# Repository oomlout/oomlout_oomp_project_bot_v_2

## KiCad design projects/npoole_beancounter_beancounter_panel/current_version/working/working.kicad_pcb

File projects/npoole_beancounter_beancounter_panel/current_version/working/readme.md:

# beancounter
 
## summary 
* id: npoole_beancounter_beancounter_panel
* user: npoole
* name: beancounter
* board: beancounter_panel
* repo: https://github.com/NPoole/BeanCounter

* src_file_repo_sch: 
* src_file_repo_sch_link: https://github.com/NPoole/BeanCounter/tree/main/
* full details link: https://github.com/oomlout/oomlout_oomp_project_bot_v_2/tree/main/projects/npoole_beancounter_beancounter_panel/current_version/working  

## pcb  

[board (pdf)](working.pdf)  

## working_bom
| Id | Designator | Footprint | Quantity | Designation | Supplier and ref |  | None | 
| --- | --- | --- | --- | --- | --- | --- | --- | 
| 1 | J5,J7,J15,J19,J10,J16,J11,J9,J23,J21,J22,J3,J8,J17,J20,J6,J4,J18 | 1X01 | 18 |  |  |  | [''] | 
| 2 | D3,D2,D4,D1 | LED-0603 | 4 | IR LED |  |  | [''] | 
| 3 | DIS3,D1S9,D2S2,D1S1,D1S12,D1S3,D2S6,D2S3,D2S1,D3S11,D1S7,D1S4,D3S10,D2S14,D3S5,D3S8,D1S6,D3S1,D1S5,D3S9,D2S8,D3S7,D1S10,D1S8,D2S11,DIS1,D2S7,D3S14,D3S13,D2S10,D3S6,D2S4,D3S2,D1S11,D2S12,D2S9,D2S13,D3S4,D3S12,D2S5,D1S2,D3S3 | LED-0603 | 42 |  |  |  | [''] | 
| 4 | R16,R3,R5,R7,R18,R2,R6,R17,R8,R21,R20,R4,R22,R19 | 0603 | 14 | 33 |  |  | [''] | 
| 5 | R26,R28,R11,R27,R14,R10,R12,R29,R9,R25,R30,R15,R23,R24,R13,R1 | 0603 | 16 | 1k |  |  | [''] | 
| 6 | E$3,E$1,E$2,E$4 | FIDUCIAL-1X2 | 4 |  |  |  | [''] | 
| 7 | Q4,Q2,Q5,Q6,Q3,Q1 | SOT23-3 | 6 | 220mA/50V/3.5Î© |  |  | [''] | 
| 8 | U$31,U$32,U$63,U$64 | HARVATEK_DETECTOR | 4 | B19H1PT |  |  | [''] | 
| 9 | @HOLE0,@HOLE1,@HOLE3,@HOLE2 |  | 4 |  |  |  | [''] | 
| 10 | U1,U2 | 32M1-A_ATM | 2 | ATTINY861V-10MU |  |  | [''] | 
| 11 | S4,S5,S1,S2 | TACTILE_SWITCH_SMD_5.2MM | 4 | MOMENTARY-SWITCH-SPST-SMD-5.2MM-TALL |  |  | [''] | 
| 12 | J12,J24,J14,J2 | 1X02 | 4 |  |  |  | [''] | 
| 13 | C3,C6,C1,C4,C2,C5 | 0603 | 6 | 0.1uF |  |  | [''] | 
| 14 | E$5,E$6 | FIDUCIAL-1.5X3 | 2 |  |  |  | [''] | 
| 15 | S6,S3 | SWITCH_SPST_SMD_A | 2 |  |  |  | [''] | 
| 16 | U$13,U$48 | BY_PRESSING_COUNT#RESET_AGAIN0 | 2 |  |  |  | [''] | 
| 17 | U$53,U$16 | TO_ENTER_COUNTING_MODE_SELECTION0 | 2 |  |  |  | [''] | 
| 18 | U$27,U$59 | #COUNT#0 | 2 |  |  |  | [''] | 
| 19 | U$26,U$58 | #COMPLETE_DOCS_AT_GITHUB#COM#NPOOLE#BEANCOUNTER#0 | 2 |  |  |  | [''] | 
| 20 | U$29,U$61 | #SETUP#0 | 2 |  |  |  | [''] | 
| 21 | U$33,U$6 | #_3V#0 | 2 |  |  |  | [''] | 
| 22 | U$4,U$49 | #PRESS_SETUP_X1#0 | 2 |  |  |  | [''] | 
| 23 | U$50,U$14 | TO_ENTER_PART_PITCH_SETUP0 | 2 |  |  |  | [''] | 
| 24 | U$25,U$57 | ALL_DIGITS_ARE_BLINKING0 | 2 |  |  |  | [''] | 
| 25 | U$36,U$20 | 40 | 2 |  |  |  | [''] | 
| 26 | U$9,U$44 | BY_PRESSING_COUNT#RESET0 | 2 |  |  |  | [''] | 
| 27 | U$24,U$40 | #OFF#EXT#0 | 2 |  |  |  | [''] | 
| 28 | U$35,U$5 | 00 | 2 |  |  |  | [''] | 
| 29 | U$47,U$12 | #RESUME_COUNTING#0 | 2 |  |  |  | [''] | 
| 30 | U$46,U$11 | #_0 | 2 |  |  |  | [''] | 
| 31 | U$39,U$23 | #ON#0 | 2 |  |  |  | [''] | 
| 32 | U$18,U$55 | #RESET_COUNTER#0 | 2 |  |  |  | [''] | 
| 33 | U$60,U$28 | #RESET#0 | 2 |  |  |  | [''] | 
| 34 | U$51,U$8 | THEN_PRESS_COUNT#RESET_TO_INCREMENT0 | 2 |  |  |  | [''] | 
| 35 | U$34,U$7 | #_GND#0 | 2 |  |  |  | [''] | 
| 36 | U$15,U$52 | #PRESS_SETUP_X2#0 | 2 |  |  |  | [''] | 
| 37 | J1,J13 | 2X3_TEST_POINTS | 2 | AVR_SPI_PROG_3X2TESTPOINTS |  |  | [''] | 
| 38 | U$37,U$21 | 120 | 2 |  |  |  | [''] | 
| 39 | U$1,U$41 | OSHWBC#SVG0 | 2 |  |  |  | [''] | 
| 40 | U$56,U$19 | BY_HOLDING_COUNT#RESET_UNTIL0 | 2 |  |  |  | [''] | 
| 41 | U$42,U$2 | EXTERN_PWR0 | 2 |  |  |  | [''] | 
| 42 | U$62,U$30 | LOGO#SVG0 | 2 |  |  |  | [''] | 
| 43 | U$22,U$38 | 160 | 2 |  |  |  | [''] | 
| 44 | BT1,BT2 | BATTCON_20MM_4LEGS_OVERPASTE_INNER | 2 |  |  |  | [''] | 
| 45 | U$17,U$54 | THEN_PRESS_COUNT#RESET_TO_SELECT0 | 2 |  |  |  | [''] | 
| 46 | U$10,U$45 | FIRST_DIGIT_WILL_BLINK_WHILE_PAUSED#_0 | 2 |  |  |  | [''] | 
| 47 | U$3,U$43 | #PAUSE_COUNTING#0 | 2 |  |  |  | [''] |

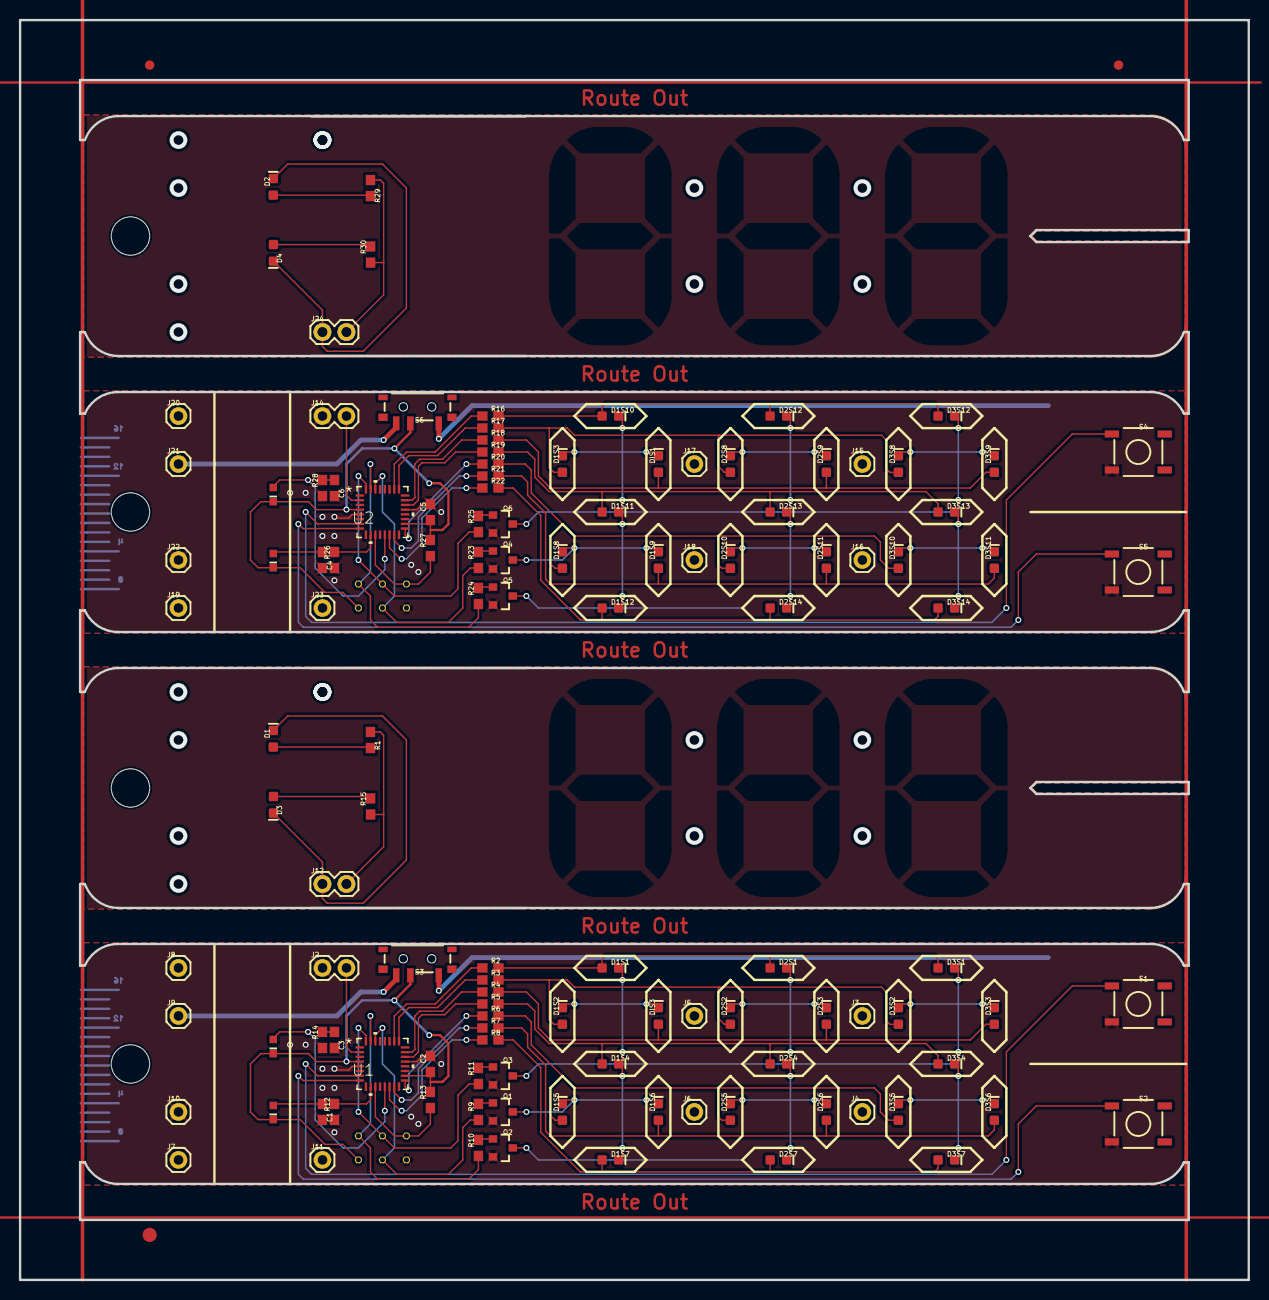
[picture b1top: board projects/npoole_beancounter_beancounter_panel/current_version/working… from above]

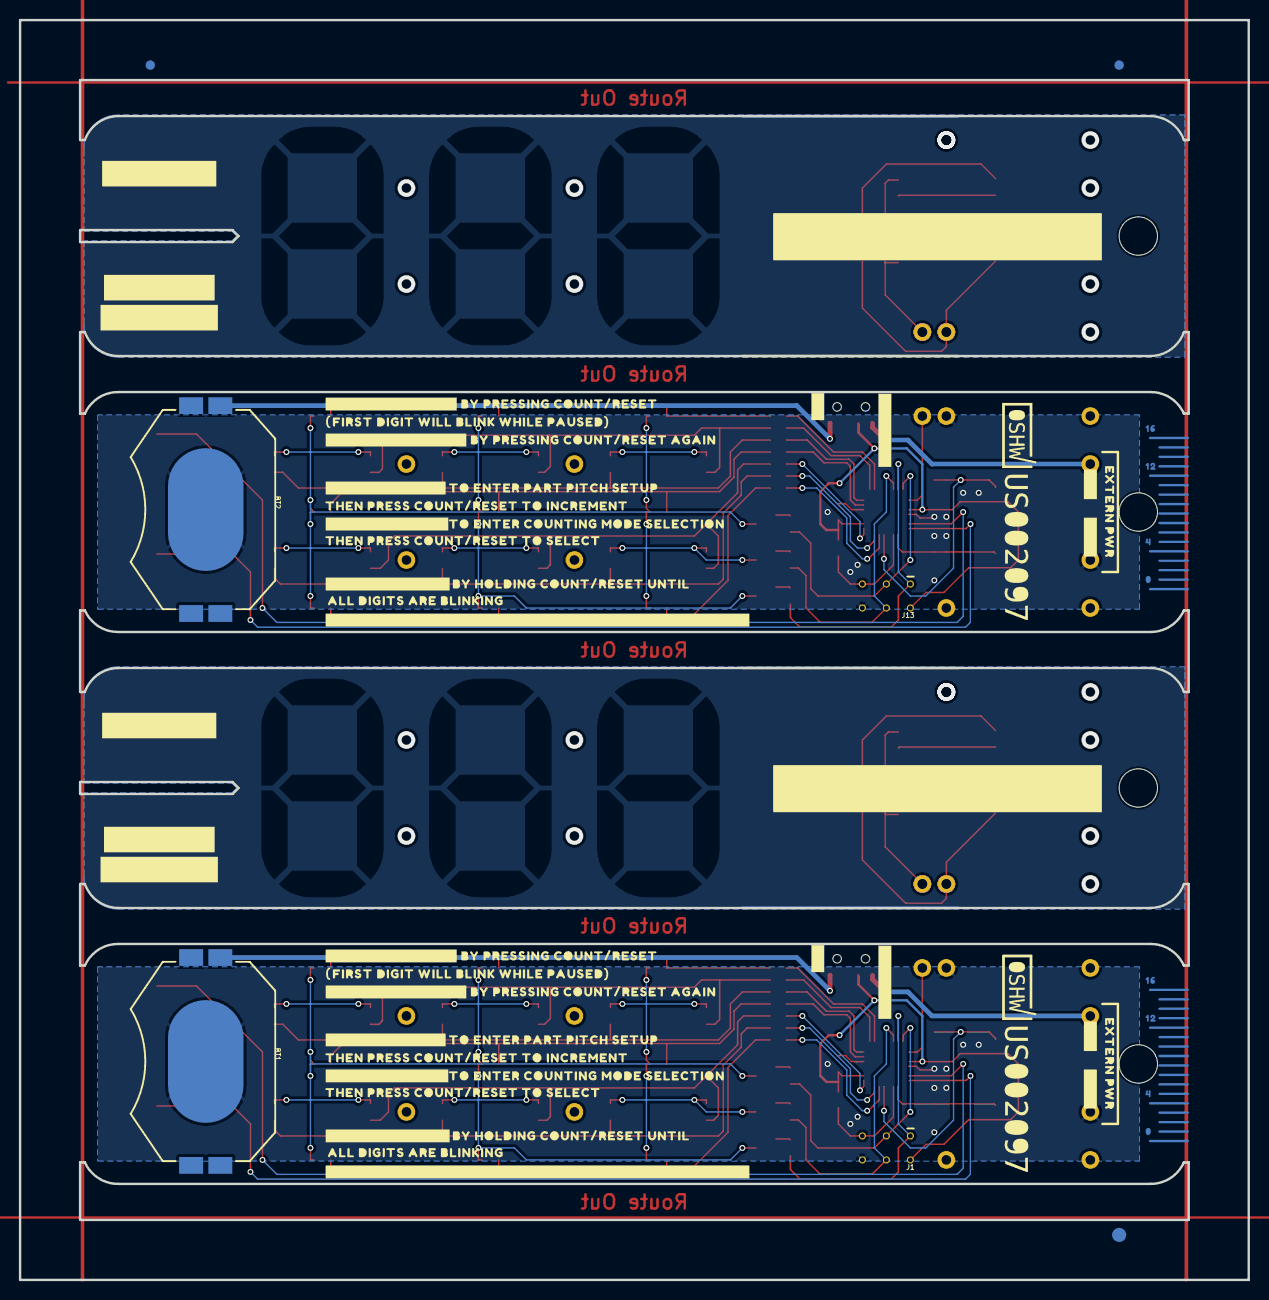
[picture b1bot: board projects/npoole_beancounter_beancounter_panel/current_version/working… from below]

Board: 2 copper layers, 130.0 x 133.3 mm, 196 parts (67 on the bottom side), 74 nets.

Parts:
@HOLE0, @HOLE1, @HOLE2, @HOLE3: (no value)
BT1, BT2: BATTCON_20MM_4LEGS_OVERPASTE_INNER
C1, C2, C3, C4, C5, C6: 0.1uF; 0603
D1, D2, D3, D4: IR LED; LED-0603
D1S1, D1S2, D1S3, D1S4, D1S5, D1S6, D1S7, D1S8, D1S9, D1S10, D1S11, D1S12, D2S1, D2S2, D2S3, D2S4, D2S5, D2S6, D2S7, D2S8, D2S9, D2S10, D2S11, D2S12, D2S13, D2S14, D3S1, D3S2, D3S3, D3S4, D3S5, D3S6, D3S7, D3S8, D3S9, D3S10, D3S11, D3S12, D3S13, D3S14: LED-0603
DIS1, DIS3: LED-0603
E$1, E$2, E$3, E$4: FIDUCIAL-1X2
E$5, E$6: FIDUCIAL-1.5X3
J1, J13: AVR_SPI_PROG_3X2TESTPOINTS; 2X3_TEST_POINTS
J2, J12, J14, J24: 1X02
J3, J4, J5, J6, J7, J8, J9, J10, J11, J15, J16, J17, J18, J19, J20, J21, J22, J23: 1X01
Q1, Q2, Q3, Q4, Q5, Q6: 220mA/50V/3.5Ω; SOT23-3
R1, R9, R10, R11, R12, R13, R14, R15, R23, R24, R25, R26, R27, R28, R29, R30: 1k; 0603
R2, R3, R4, R5, R6, R7, R8, R16, R17, R18, R19, R20, R21, R22: 33; 0603
S1, S2, S4, S5: MOMENTARY-SWITCH-SPST-SMD-5.2MM-TALL; TACTILE_SWITCH_SMD_5.2MM
S3, S6: SWITCH_SPST_SMD_A
U1, U2: ATTINY861V-10MU; 32M1-A_ATM
U$1, U$41: OSHWBC#SVG0
U$2, U$42: EXTERN_PWR0
U$3, U$43: #PAUSE_COUNTING#0
U$4, U$49: #PRESS_SETUP_X1#0
U$5, U$35: 00
U$6, U$33: #_3V#0
U$7, U$34: #_GND#0
U$8, U$51: THEN_PRESS_COUNT#RESET_TO_INCREMENT0
U$9, U$44: BY_PRESSING_COUNT#RESET0
U$10, U$45: FIRST_DIGIT_WILL_BLINK_WHILE_PAUSED#_0
U$11, U$46: #_0
U$12, U$47: #RESUME_COUNTING#0
U$13, U$48: BY_PRESSING_COUNT#RESET_AGAIN0
U$14, U$50: TO_ENTER_PART_PITCH_SETUP0
U$15, U$52: #PRESS_SETUP_X2#0
U$16, U$53: TO_ENTER_COUNTING_MODE_SELECTION0
U$17, U$54: THEN_PRESS_COUNT#RESET_TO_SELECT0
U$18, U$55: #RESET_COUNTER#0
U$19, U$56: BY_HOLDING_COUNT#RESET_UNTIL0
U$20, U$36: 40
U$21, U$37: 120
U$22, U$38: 160
U$23, U$39: #ON#0
U$24, U$40: #OFF#EXT#0
U$25, U$57: ALL_DIGITS_ARE_BLINKING0
U$26, U$58: #COMPLETE_DOCS_AT_GITHUB#COM#NPOOLE#BEANCOUNTER#0
U$27, U$59: #COUNT#0
U$28, U$60: #RESET#0
U$29, U$61: #SETUP#0
U$30, U$62: LOGO#SVG0
U$31, U$32, U$63, U$64: B19H1PT; HARVATEK_DETECTOR

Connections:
0: R2.1, U1.26
1: R3.1, U1.25
2: R4.1, U1.23
3: R5.1, U1.22
4: R6.1, U1.17
5: R7.1, U1.15
6: R8.1, U1.14
8/COPI: J1.4, R9.1, U1.30
9/CIPO: J1.1, R10.1, U1.31
10/SCK: J1.3, R11.1, U1.32
11: J2.2, U1.2
12: S1.1, U1.7
13: S2.1, U1.8
GND: BT1.2, C1.2, C2.2, C3.2, J1.6, J2.1, J10.1, Q1.2, Q2.2, Q3.2, R12.1, R14.1, S1.3, S2.3, U1.5, U1.21
IR_DETECTOR_A: C1.1, R12.2, U1.10, U$31.P$2
IR_DETECTOR_B: C3.1, R14.2, U1.13, U$32.P$2
unnamed: BT1.1, S3.3
unnamed: D1S1.C, D1S2.C, D1S4.C, D1S5.C, D1S6.C, D1S7.C, DIS3.C, Q1.3
unnamed: Q2.1, R10.2
unnamed: Q1.1, R9.2
unnamed: D2S1.C, D2S2.C, D2S3.C, D2S4.C, D2S5.C, D2S6.C, D2S7.C, Q2.3
unnamed: Q3.1, R11.2
unnamed: D3S1.C, D3S2.C, D3S3.C, D3S4.C, D3S5.C, D3S6.C, D3S7.C, Q3.3
unnamed: C6.1, R28.2, U2.13, U$64.P$2
unnamed: J24.2, R29.1, R30.1
unnamed: D2.C, D4.C, J24.1
unnamed: J12.2, R1.1, R15.1
unnamed: D1.C, D3.C, J12.1
unnamed: D3.A, R15.2
unnamed: D1.A, R1.2
unnamed: BT2.2, C4.2, C5.2, C6.2, J13.6, J14.1, J22.1, Q4.2, Q5.2, Q6.2, R26.1, R28.1, S4.3, S5.3, U2.5, U2.21
unnamed: C5.1, J13.2, R27.2, S6.2, U2.4, U2.18, U$63.P$1, U$64.P$1
unnamed: Q4.1, R23.2
unnamed: D1S3.C, D1S8.C, D1S9.C, D1S10.C, D1S11.C, D1S12.C, DIS1.C, Q4.3
unnamed: D2S8.C, D2S9.C, D2S10.C, D2S11.C, D2S12.C, D2S13.C, D2S14.C, Q5.3
unnamed: D3S8.C, D3S9.C, D3S10.C, D3S11.C, D3S12.C, D3S13.C, D3S14.C, Q6.3
unnamed: Q5.1, R24.2
unnamed: Q6.1, R25.2
unnamed: D1S10.A, D2S12.A, D3S12.A, R16.2
unnamed: D1S11.A, D2S13.A, D3S13.A, R19.2
unnamed: D1S3.A, D2S8.A, D3S8.A, R17.2
unnamed: D2S9.A, D3S9.A, DIS1.A, R18.2
unnamed: D1S9.A, D2S11.A, D3S11.A, R21.2
unnamed: D1S8.A, D2S10.A, D3S10.A, R20.2
unnamed: D1S12.A, D2S14.A, D3S14.A, R22.2
unnamed: C4.1, R26.2, U2.10, U$63.P$2
unnamed: J13.5, R27.1, U2.11
unnamed: R16.1, U2.26
unnamed: R17.1, U2.25
unnamed: R18.1, U2.23
unnamed: R19.1, U2.22
unnamed: R20.1, U2.17
unnamed: R21.1, U2.15
unnamed: R22.1, U2.14
unnamed: J13.4, R23.1, U2.30
unnamed: J13.1, R24.1, U2.31
unnamed: J13.3, R25.1, U2.32
unnamed: J14.2, U2.2
unnamed: S4.1, U2.7
unnamed: S5.1, U2.8
unnamed: J21.1, S6.1
unnamed: BT2.1, S6.3
SEG1: D1S1.A, D2S1.A, D3S1.A, R2.2
SEG2: D1S2.A, D2S2.A, D3S2.A, R3.2
SEG3: D2S3.A, D3S3.A, DIS3.A, R4.2
SEG4: D1S4.A, D2S4.A, D3S4.A, R5.2
SEG5: D1S5.A, D2S5.A, D3S5.A, R6.2
SEG6: D1S6.A, D2S6.A, D3S6.A, R7.2
SEG7: D1S7.A, D2S7.A, D3S7.A, R8.2
SEG9: D4.A, R30.2
SEG10: D2.A, R29.2
V_BATT: C2.1, J1.2, R13.2, S3.2, U1.4, U1.18, U$31.P$1, U$32.P$1
V_EXT: J9.1, S3.1
~RESET: J1.5, R13.1, U1.11

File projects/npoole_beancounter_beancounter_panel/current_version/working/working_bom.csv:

"Id";"Designator";"Footprint";"Quantity";"Designation";"Supplier and ref";
1;"J5,J7,J15,J19,J10,J16,J11,J9,J23,J21,J22,J3,J8,J17,J20,J6,J4,J18";"1X01";18;"";;;
2;"D3,D2,D4,D1";"LED-0603";4;"IR LED";;;
3;"DIS3,D1S9,D2S2,D1S1,D1S12,D1S3,D2S6,D2S3,D2S1,D3S11,D1S7,D1S4,D3S10,D2S14,D3S5,D3S8,D1S6,D3S1,D1S5,D3S9,D2S8,D3S7,D1S10,D1S8,D2S11,DIS1,D2S7,D3S14,D3S13,D2S10,D3S6,D2S4,D3S2,D1S11,D2S12,D2S9,D2S13,D3S4,D3S12,D2S5,D1S2,D3S3";"LED-0603";42;"";;;
4;"R16,R3,R5,R7,R18,R2,R6,R17,R8,R21,R20,R4,R22,R19";"0603";14;"33";;;
5;"R26,R28,R11,R27,R14,R10,R12,R29,R9,R25,R30,R15,R23,R24,R13,R1";"0603";16;"1k";;;
6;"E$3,E$1,E$2,E$4";"FIDUCIAL-1X2";4;"";;;
7;"Q4,Q2,Q5,Q6,Q3,Q1";"SOT23-3";6;"220mA/50V/3.5Ω";;;
8;"U$31,U$32,U$63,U$64";"HARVATEK_DETECTOR";4;"B19H1PT";;;
9;"@HOLE0,@HOLE1,@HOLE3,@HOLE2";"";4;"";;;
10;"U1,U2";"32M1-A_ATM";2;"ATTINY861V-10MU";;;
11;"S4,S5,S1,S2";"TACTILE_SWITCH_SMD_5.2MM";4;"MOMENTARY-SWITCH-SPST-SMD-5.2MM-TALL";;;
12;"J12,J24,J14,J2";"1X02";4;"";;;
13;"C3,C6,C1,C4,C2,C5";"0603";6;"0.1uF";;;
14;"E$5,E$6";"FIDUCIAL-1.5X3";2;"";;;
15;"S6,S3";"SWITCH_SPST_SMD_A";2;"";;;
16;"U$13,U$48";"BY_PRESSING_COUNT#RESET_AGAIN0";2;"";;;
17;"U$53,U$16";"TO_ENTER_COUNTING_MODE_SELECTION0";2;"";;;
18;"U$27,U$59";"#COUNT#0";2;"";;;
19;"U$26,U$58";"#COMPLETE_DOCS_AT_GITHUB#COM#NPOOLE#BEANCOUNTER#0";2;"";;;
20;"U$29,U$61";"#SETUP#0";2;"";;;
21;"U$33,U$6";"#_3V#0";2;"";;;
22;"U$4,U$49";"#PRESS_SETUP_X1#0";2;"";;;
23;"U$50,U$14";"TO_ENTER_PART_PITCH_SETUP0";2;"";;;
24;"U$25,U$57";"ALL_DIGITS_ARE_BLINKING0";2;"";;;
25;"U$36,U$20";"40";2;"";;;
26;"U$9,U$44";"BY_PRESSING_COUNT#RESET0";2;"";;;
27;"U$24,U$40";"#OFF#EXT#0";2;"";;;
28;"U$35,U$5";"00";2;"";;;
29;"U$47,U$12";"#RESUME_COUNTING#0";2;"";;;
30;"U$46,U$11";"#_0";2;"";;;
31;"U$39,U$23";"#ON#0";2;"";;;
32;"U$18,U$55";"#RESET_COUNTER#0";2;"";;;
33;"U$60,U$28";"#RESET#0";2;"";;;
34;"U$51,U$8";"THEN_PRESS_COUNT#RESET_TO_INCREMENT0";2;"";;;
35;"U$34,U$7";"#_GND#0";2;"";;;
36;"U$15,U$52";"#PRESS_SETUP_X2#0";2;"";;;
37;"J1,J13";"2X3_TEST_POINTS";2;"AVR_SPI_PROG_3X2TESTPOINTS";;;
38;"U$37,U$21";"120";2;"";;;
39;"U$1,U$41";"OSHWBC#SVG0";2;"";;;
40;"U$56,U$19";"BY_HOLDING_COUNT#RESET_UNTIL0";2;"";;;
41;"U$42,U$2";"EXTERN_PWR0";2;"";;;
42;"U$62,U$30";"LOGO#SVG0";2;"";;;
43;"U$22,U$38";"160";2;"";;;
44;"BT1,BT2";"BATTCON_20MM_4LEGS_OVERPASTE_INNER";2;"";;;
45;"U$17,U$54";"THEN_PRESS_COUNT#RESET_TO_SELECT0";2;"";;;
46;"U$10,U$45";"FIRST_DIGIT_WILL_BLINK_WHILE_PAUSED#_0";2;"";;;
47;"U$3,U$43";"#PAUSE_COUNTING#0";2;"";;;

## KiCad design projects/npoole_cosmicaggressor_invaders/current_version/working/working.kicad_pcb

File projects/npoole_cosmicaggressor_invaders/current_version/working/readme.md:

# cosmicaggressor
 
## summary 
* id: npoole_cosmicaggressor_invaders
* user: npoole
* name: cosmicaggressor
* board: invaders
* repo: https://github.com/NPoole/CosmicAggressor

* src_file_repo_sch: 
* src_file_repo_sch_link: https://github.com/NPoole/CosmicAggressor/tree/master/
* full details link: https://github.com/oomlout/oomlout_oomp_project_bot_v_2/tree/main/projects/npoole_cosmicaggressor_invaders/current_version/working  

## schematic  
  
[schematic (pdf)](working_schematic.pdf) 

## pcb  

[board (pdf)](working.pdf)  

## working_bom
| Id | Designator | Footprint | Quantity | Designation | Supplier and ref |  | None | 
| --- | --- | --- | --- | --- | --- | --- | --- | 
| 1 | D72,D84,D8,D46,D67,D22,D29,D92,D126,D20,D68,D66,D52,D87,D108,D99,D95,D2,D57,D100,D127,D120,D117,D38,D102,D137,D31,D61,D17,D3,D65,D121,D37,D30,D85,D103,D98,D33,D140,D79,D41,D1,D81,D77,D40,D11,D75,D19,D47,D74,D62,D49,D93,D128,D109,D141,D143,D42,D56,D54,D71,D115,D78,D111,D124,D114,D110,D50,D144,D24,D26,D5,D107,D35,D4,D76,D43,D28,D7,D104,D45,D101,D63,D90,D122,D60,D51,D15,D55,D16,D116,D48,D39,D80,D34,D23,D32,D123,D112,D12,D96,D105,D10,D142,D58,D113,D9,D25,D125,D106,D94,D53,D86,D139,D36,D118,D18,D44,D13,D64,D73,D59,D138,D69,D21,D6,D27,D82,D70,D119,D91,D89,D97,D88,D83,D14 | APA102-2020 | 136 | APA102-2020 |  |  | [''] | 
| 2 | C9,C10 | 0603 | 2 | 4.7uF |  |  | [''] | 
| 3 | U2 | SOT23-5 | 1 | MCP73831 |  |  | [''] | 
| 4 | R3,R2 | 0603@1 | 2 | 22 |  |  | [''] | 
| 5 | Y1 | CRYSTAL-SMD-5X3.2-4PAD | 1 | 16MHz |  |  | [''] | 
| 6 | R1 | 0603@1 | 1 | 10k |  |  | [''] | 
| 7 | BT1 | BATTERY_18650-HOLDER | 1 |  |  |  | [''] | 
| 8 | J9,J6,J5,J8,J4,J7,J2,J3 | 1X01NS_KIT | 8 |  |  |  | [''] | 
| 9 | D131,D130 | SMA-DIODE | 2 | 3A/40V/500mV |  |  | [''] | 
| 10 | C2,C3 | 0603 | 2 | 1.0uF |  |  | [''] | 
| 11 | C8,C6,C7 | 0805 | 3 | 22uF |  |  | [''] | 
| 12 | C4,C5 | 0603 | 2 | 18pF |  |  | [''] | 
| 13 | R6,R4 | 0603 | 2 | 750K |  |  | [''] | 
| 14 | RPROG0 | 0603 | 1 | 2.0k |  |  | [''] | 
| 15 | R5 | 0603 | 1 | 100k |  |  | [''] | 
| 16 | C1 | 0603 | 1 | 0.1uF |  |  | [''] | 
| 17 | U3 | MSOP8 | 1 | PAM2401 |  |  | [''] | 
| 18 | L1 | INDUCTOR_4X4MM | 1 | 2.2UH3A |  |  | [''] | 
| 19 | J1 | USB-MICROB-PTH-MILL | 1 |  |  |  | [''] | 
| 20 | U1 | QFN-44-NOPAD_1_1-LESS_PASTE | 1 | 32U4 |  |  | [''] | 
| 21 | S2 | SWITCH_DPDT_SMD_AYZ0202 | 1 |  |  |  | [''] | 
| 22 | U$1 | COSMIC_AGGRESSOR0 | 1 |  |  |  | [''] | 
| 23 | J10 | 2X3 | 1 | AVR_SPI_PROG_3X2PTH |  |  | [''] | 
| 24 | U$2 | #NORTHALLENPOOLE1 | 1 |  |  |  | [''] | 
| 25 | U$4 | OSHW-LOGO-S | 1 |  |  |  | [''] | 
| 26 | U$3 | HTTPS###GITHUB#COM#NPOOLE#COSMICAGGRESSOR2 | 1 |  |  |  | [''] | 

## bom_schematic
| Ref | Qnty | Value | Cmp name | Footprint | Description | Vendor | DNP | 
| --- | --- | --- | --- | --- | --- | --- | --- | 
| BT1 | 1 | BATTERY-18650 | BATTERY-18650 | working:BATTERY_18650-HOLDER |  |  |  | 
| C1 | 1 | 0.1UF-0603-25V-(+80/-20%) | 0.1UF-0603-25V-(+80/-20%) | working:0603 |  |  |  | 
| C2, C3 | 2 | 1.0UF-0603-16V-10% | 1.0UF-0603-16V-10% | working:0603 |  |  |  | 
| C4, C5 | 2 | 18PF-0603-50V-5% | 18PF-0603-50V-5% | working:0603 |  |  |  | 
| C6, C7, C8 | 3 | 22UF-0805-6.3V-20% | 22UF-0805-6.3V-20% | working:0805 |  |  |  | 
| C9, C10 | 2 | 4.7UF0603 | 4.7UF0603 | working:0603 |  |  |  | 
| D1, D2, D3, D4, D5, D6, D7, D8, D9, D10, D11, D12, D13, D14, D15, D16, D17, D18, D19, D20, D21, D22, D23, D24, D25, D26, D27, D28, D29, D30, D31, D32, D33, D34, D35, D36, D37, D38, D39, D40, D41, D42, D43, D44, D45, D46, D47, D48, D49, D50, D51, D52, D53, D54, D55, D56, D57, D58, D59, D60, D61, D62, D63, D64, D65, D66, D67, D68, D69, D70, D71, D72, D73, D74, D75, D76, D77, D78, D79, D80, D81, D82, D83, D84, D85, D86, D87, D88, D89, D90, D91, D92, D93, D94, D95, D96, D97, D98, D99, D100, D101, D102, D103, D104, D105, D106, D107, D108, D109, D110, D111, D112, D113, D114, D115, D116, D117, D118, D119, D120, D121, D122, D123, D124, D125, D126, D127, D128, D137, D138, D139, D140, D141, D142, D143, D144 | 136 | APA102-2020 | APA102-2020 | working:APA102-2020 |  |  |  | 
| D130, D131 | 2 | DIODE-SCHOTTKY-B340A | DIODE-SCHOTTKY-B340A | working:SMA-DIODE |  |  |  | 
| J1 | 1 | USB_MICRO-B_HALF_PTH_MILL | USB_MICRO-B_HALF_PTH_MILL | working:USB-MICROB-PTH-MILL |  |  |  | 
| J2, J3, J4, J5, J6, J7, J8, J9 | 8 | CONN_01PTH_NO_SILK_KIT | CONN_01PTH_NO_SILK_KIT | working:1X01NS_KIT |  |  |  | 
| J10 | 1 | AVR_SPI_PROG_3X2PTH | AVR_SPI_PROG_3X2PTH | working:2X3 |  |  |  | 
| L1 | 1 | INDUCTOR-IFSC1515AHER2R2M01 | INDUCTOR-IFSC1515AHER2R2M01 | working:INDUCTOR_4X4MM |  |  |  | 
| R1 | 1 | 10KOHM-0603-1/10W-1% | 10KOHM-0603-1/10W-1% | working:0603@1 |  |  |  | 
| R2, R3 | 2 | 22OHM-0603-1/10W-1% | 22OHM-0603-1/10W-1% | working:0603@1 |  |  |  | 
| R4, R6 | 2 | 750KOHM-0603-1/10W-1% | 750KOHM-0603-1/10W-1% | working:0603 |  |  |  | 
| R5 | 1 | 100KOHM-0603-1/10W-1% | 100KOHM-0603-1/10W-1% | working:0603 |  |  |  | 
| RPROG0 | 1 | 2.0KOHM-0603-1/10W-5% | 2.0KOHM-0603-1/10W-5% | working:0603 |  |  |  | 
| S2 | 1 | SWITCH-DPDT-SMD-AYZ0202 | SWITCH-DPDT-SMD-AYZ0202 | working:SWITCH_DPDT_SMD_AYZ0202 |  |  |  | 
| U1 | 1 | ATMEGA32U41:1-LESS_PASTE | ATMEGA32U41{colon}1-LESS_PASTE | working:QFN-44-NOPAD_1_1-LESS_PASTE |  |  |  | 
| U2 | 1 | MCP73831 | MCP73831 | working:SOT23-5 |  |  |  | 
| U3 | 1 | PAM2401 | PAM2401 | working:MSOP8 |  |  |  | 
| Y1 | 1 | 16MHz | CRYSTAL-16MHZSMD-5X3.2 | working:CRYSTAL-SMD-5X3.2-4PAD |  |  |  |

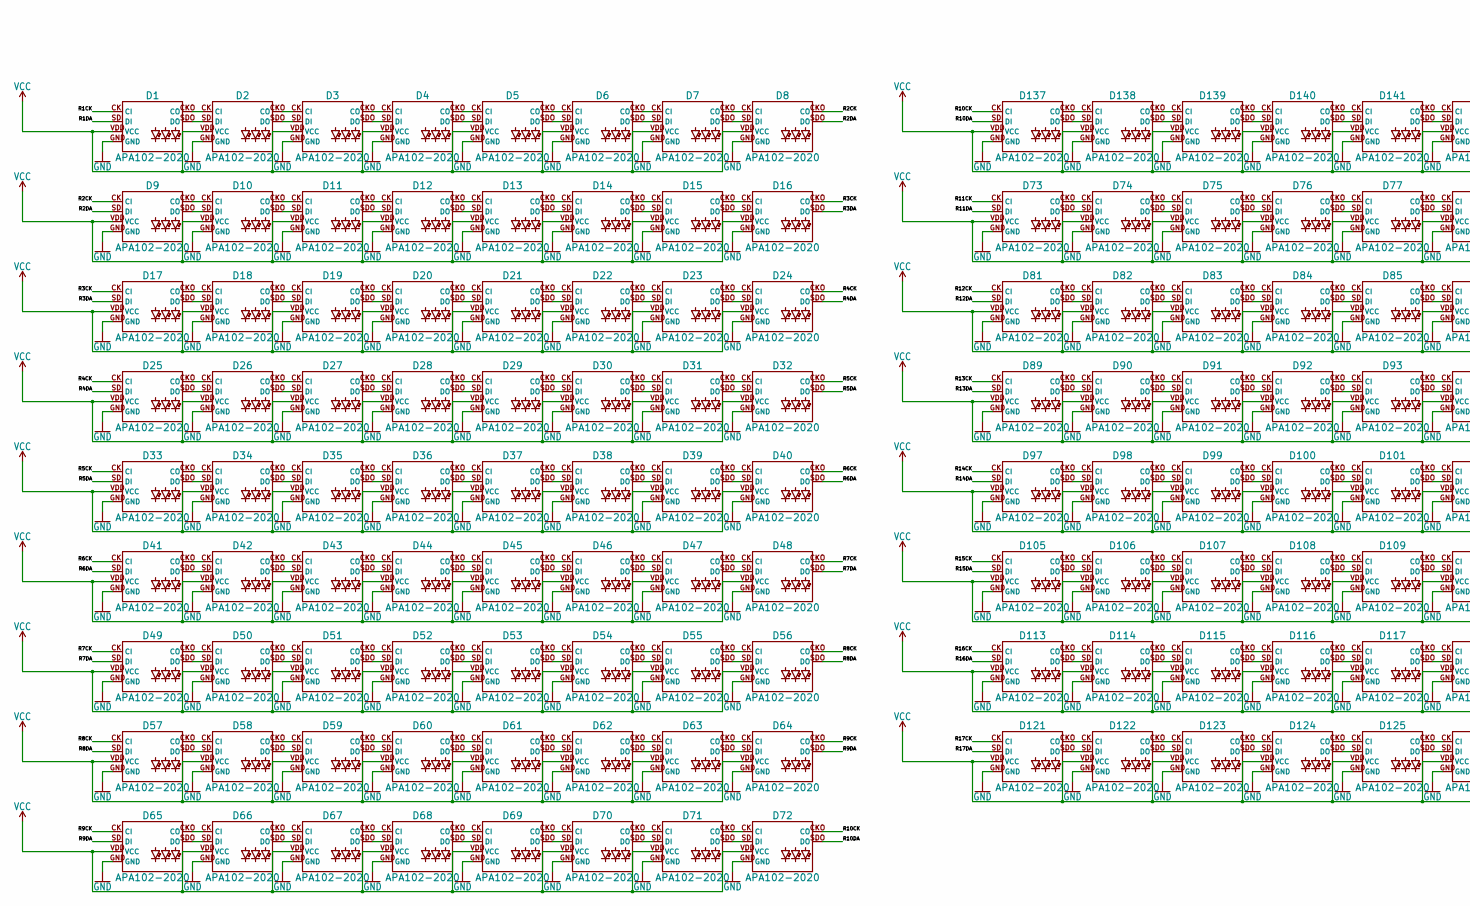
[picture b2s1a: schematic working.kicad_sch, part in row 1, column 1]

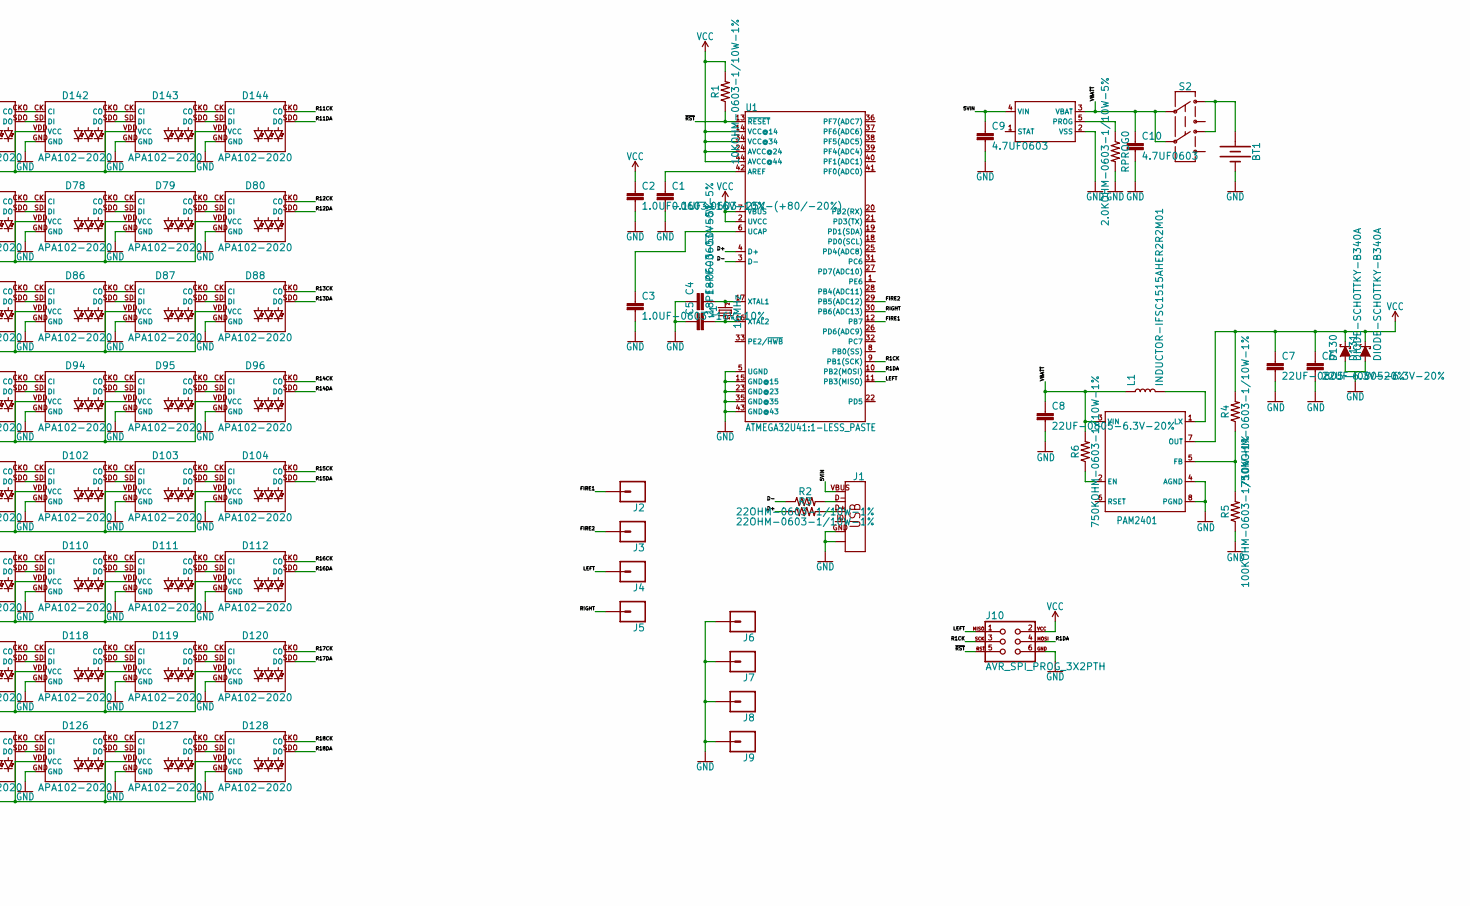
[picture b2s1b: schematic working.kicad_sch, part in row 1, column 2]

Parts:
BT1: BATTERY-18650; BATTERY_18650-HOLDER
C1: 0.1UF-0603-25V-(+80/-20%); 0603
C2, C3: 1.0UF-0603-16V-10%; 0603
C4, C5: 18PF-0603-50V-5%; 0603
C6, C7, C8: 22UF-0805-6.3V-20%; 0805
C9, C10: 4.7UF0603; 0603
D1, D2, D3, D4, D5, D6, D7, D8, D9, D10, D11, D12, D13, D14, D15, D16, D17, D18, D19, D20, D21, D22, D23, D24, D25, D26, D27, D28, D29, D30, D31, D32, D33, D34, D35, D36, D37, D38, D39, D40, D41, D42, D43, D44, D45, D46, D47, D48, D49, D50, D51, D52, D53, D54, D55, D56, D57, D58, D59, D60, D61, D62, D63, D64, D65, D66, D67, D68, D69, D70, D71, D72, D73, D74, D75, D76, D77, D78, D79, D80, D81, D82, D83, D84, D85, D86, D87, D88, D89, D90, D91, D92, D93, D94, D95, D96, D97, D98, D99, D100, D101, D102, D103, D104, D105, D106, D107, D108, D109, D110, D111, D112, D113, D114, D115, D116, D117, D118, D119, D120, D121, D122, D123, D124, D125, D126, D127, D128, D137, D138, D139, D140, D141, D142, D143, D144: APA102-2020
D130, D131: DIODE-SCHOTTKY-B340A; SMA-DIODE
J1: USB_MICRO-B_HALF_PTH_MILL; USB-MICROB-PTH-MILL
J2, J3, J4, J5, J6, J7, J8, J9: CONN_01PTH_NO_SILK_KIT; 1X01NS_KIT
J10: AVR_SPI_PROG_3X2PTH; 2X3
L1: INDUCTOR-IFSC1515AHER2R2M01; INDUCTOR_4X4MM
R1: 10KOHM-0603-1/10W-1%; 0603@1
R2, R3: 22OHM-0603-1/10W-1%; 0603@1
R4, R6: 750KOHM-0603-1/10W-1%; 0603
R5: 100KOHM-0603-1/10W-1%; 0603
RPROG0: 2.0KOHM-0603-1/10W-5%; 0603
S2: SWITCH-DPDT-SMD-AYZ0202; SWITCH_DPDT_SMD_AYZ0202
U1: ATMEGA32U41:1-LESS_PASTE; QFN-44-NOPAD_1_1-LESS_PASTE
U2: MCP73831; SOT23-5
U3: PAM2401; MSOP8
Y1: 16MHz; CRYSTAL-SMD-5X3.2-4PAD

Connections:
5VIN: C9.1, J1.VBUS, U2.4 (VIN)
D+: R3.1, U1.4 (D+)
D-: R2.1, U1.3 (D-)
EN: R6.1, U3.2 (EN)
FIRE1: J2.1, U1.12 (PB7)
FIRE2: J3.1, U1.29 (PB5(ADC12))
GND: BT1.GND@1 (-), C1.2, C2.2, C3.2, C4.1, C5.1, C6.2, C7.2, C8.2, C9.2, C10.2, D1.GND, D2.GND, D3.GND, D4.GND, D5.GND, D6.GND, D7.GND, D8.GND, D9.GND, D10.GND, D11.GND, D12.GND, D13.GND, D14.GND, D15.GND, D16.GND, D17.GND, D18.GND, D19.GND, D20.GND, D21.GND, D22.GND, D23.GND, D24.GND, D25.GND, D26.GND, D27.GND, D28.GND, D29.GND, D30.GND, D31.GND, D32.GND, D33.GND, D34.GND, D35.GND, D36.GND, D37.GND, D38.GND, D39.GND, D40.GND, D41.GND, D42.GND, D43.GND, D44.GND, D45.GND, D46.GND, D47.GND, D48.GND, D49.GND, D50.GND, D51.GND, D52.GND, D53.GND, D54.GND, D55.GND, D56.GND, D57.GND, D58.GND, D59.GND, D60.GND, D61.GND, D62.GND, D63.GND, D64.GND, D65.GND, D66.GND, D67.GND, D68.GND, D69.GND, D70.GND, D71.GND, D72.GND, D73.GND, D74.GND, D75.GND, D76.GND, D77.GND, D78.GND, D79.GND, D80.GND, D81.GND, D82.GND, D83.GND, D84.GND, D85.GND, D86.GND, D87.GND, D88.GND, D89.GND, D90.GND, D91.GND, D92.GND, D93.GND, D94.GND, D95.GND, D96.GND, D97.GND, D98.GND, D99.GND, D100.GND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
LEFT: J4.1, J10.1, U1.11 (PB3(MISO))
unnamed: D73.CKO (CO), D74.CKI (CI)
unnamed: D73.SDO (DO), D74.SDI (DI)
unnamed: D1.CKO (CO), D2.CKI (CI)
unnamed: D1.SDO (DO), D2.SDI (DI)
unnamed: D2.CKO (CO), D3.CKI (CI)
unnamed: D2.SDO (DO), D3.SDI (DI)
unnamed: D3.CKO (CO), D4.CKI (CI)
unnamed: D3.SDO (DO), D4.SDI (DI)
unnamed: D4.CKO (CO), D5.CKI (CI)
unnamed: D4.SDO (DO), D5.SDI (DI)
unnamed: D5.CKO (CO), D6.CKI (CI)
unnamed: D5.SDO (DO), D6.SDI (DI)
unnamed: D6.CKO (CO), D7.CKI (CI)
unnamed: D6.SDO (DO), D7.SDI (DI)
unnamed: D7.CKO (CO), D8.CKI (CI)
unnamed: D7.SDO (DO), D8.SDI (DI)
unnamed: D74.CKO (CO), D75.CKI (CI)
unnamed: D74.SDO (DO), D75.SDI (DI)
unnamed: D75.CKO (CO), D76.CKI (CI)
unnamed: D75.SDO (DO), D76.SDI (DI)
unnamed: D9.CKO (CO), D10.CKI (CI)
unnamed: D9.SDO (DO), D10.SDI (DI)
unnamed: D10.CKO (CO), D11.CKI (CI)
unnamed: D10.SDO (DO), D11.SDI (DI)
unnamed: D11.CKO (CO), D12.CKI (CI)
unnamed: D11.SDO (DO), D12.SDI (DI)
unnamed: D12.CKO (CO), D13.CKI (CI)
unnamed: D12.SDO (DO), D13.SDI (DI)
unnamed: D13.CKO (CO), D14.CKI (CI)
unnamed: D13.SDO (DO), D14.SDI (DI)
unnamed: D14.CKO (CO), D15.CKI (CI)
unnamed: D14.SDO (DO), D15.SDI (DI)
unnamed: D15.CKO (CO), D16.CKI (CI)
unnamed: D15.SDO (DO), D16.SDI (DI)
unnamed: D76.CKO (CO), D77.CKI (CI)
unnamed: D76.SDO (DO), D77.SDI (DI)
unnamed: D77.CKO (CO), D78.CKI (CI)
unnamed: D77.SDO (DO), D78.SDI (DI)
unnamed: D17.CKO (CO), D18.CKI (CI)
unnamed: D17.SDO (DO), D18.SDI (DI)
unnamed: D18.CKO (CO), D19.CKI (CI)
unnamed: D18.SDO (DO), D19.SDI (DI)
unnamed: D19.CKO (CO), D20.CKI (CI)
unnamed: D19.SDO (DO), D20.SDI (DI)
unnamed: D20.CKO (CO), D21.CKI (CI)
unnamed: D20.SDO (DO), D21.SDI (DI)
unnamed: D21.CKO (CO), D22.CKI (CI)
unnamed: D21.SDO (DO), D22.SDI (DI)
unnamed: D22.CKO (CO), D23.CKI (CI)
unnamed: D22.SDO (DO), D23.SDI (DI)
unnamed: D23.CKO (CO), D24.CKI (CI)
unnamed: D23.SDO (DO), D24.SDI (DI)
unnamed: D78.CKO (CO), D79.CKI (CI)
unnamed: D78.SDO (DO), D79.SDI (DI)
unnamed: D79.CKO (CO), D80.CKI (CI)
unnamed: D79.SDO (DO), D80.SDI (DI)
unnamed: D25.CKO (CO), D26.CKI (CI)
unnamed: D25.SDO (DO), D26.SDI (DI)
unnamed: D26.CKO (CO), D27.CKI (CI)
unnamed: D26.SDO (DO), D27.SDI (DI)
unnamed: D27.CKO (CO), D28.CKI (CI)
unnamed: D27.SDO (DO), D28.SDI (DI)
unnamed: D28.CKO (CO), D29.CKI (CI)
unnamed: D28.SDO (DO), D29.SDI (DI)
unnamed: D29.CKO (CO), D30.CKI (CI)
unnamed: D29.SDO (DO), D30.SDI (DI)
unnamed: D30.CKO (CO), D31.CKI (CI)
unnamed: D30.SDO (DO), D31.SDI (DI)
unnamed: D31.CKO (CO), D32.CKI (CI)
unnamed: D31.SDO (DO), D32.SDI (DI)
unnamed: D39.CKO (CO), D40.CKI (CI)
unnamed: D39.SDO (DO), D40.SDI (DI)
unnamed: D38.SDO (DO), D39.SDI (DI)
unnamed: D38.CKO (CO), D39.CKI (CI)
unnamed: D37.SDO (DO), D38.SDI (DI)
unnamed: D37.CKO (CO), D38.CKI (CI)
unnamed: D36.SDO (DO), D37.SDI (DI)
unnamed: D36.CKO (CO), D37.CKI (CI)
unnamed: D35.SDO (DO), D36.SDI (DI)
unnamed: D35.CKO (CO), D36.CKI (CI)
unnamed: D34.SDO (DO), D35.SDI (DI)
unnamed: D34.CKO (CO), D35.CKI (CI)
unnamed: D33.CKO (CO), D34.CKI (CI)
unnamed: D33.SDO (DO), D34.SDI (DI)
unnamed: D81.CKO (CO), D82.CKI (CI)
unnamed: D81.SDO (DO), D82.SDI (DI)
unnamed: D82.CKO (CO), D83.CKI (CI)
unnamed: D82.SDO (DO), D83.SDI (DI)
unnamed: D83.CKO (CO), D84.CKI (CI)
unnamed: D83.SDO (DO), D84.SDI (DI)
unnamed: D84.CKO (CO), D85.CKI (CI)
unnamed: D84.SDO (DO), D85.SDI (DI)
unnamed: D85.CKO (CO), D86.CKI (CI)
unnamed: D85.SDO (DO), D86.SDI (DI)
unnamed: D41.CKO (CO), D42.CKI (CI)
unnamed: D41.SDO (DO), D42.SDI (DI)
unnamed: D42.CKO (CO), D43.CKI (CI)
unnamed: D42.SDO (DO), D43.SDI (DI)
unnamed: D43.CKO (CO), D44.CKI (CI)
unnamed: D43.SDO (DO), D44.SDI (DI)
unnamed: D44.CKO (CO), D45.CKI (CI)
unnamed: D44.SDO (DO), D45.SDI (DI)
unnamed: D45.SDO (DO), D46.SDI (DI)
unnamed: D45.CKO (CO), D46.CKI (CI)
unnamed: D46.CKO (CO), D47.CKI (CI)
unnamed: D46.SDO (DO), D47.SDI (DI)
unnamed: D47.CKO (CO), D48.CKI (CI)
unnamed: D47.SDO (DO), D48.SDI (DI)
unnamed: D86.CKO (CO), D87.CKI (CI)
unnamed: D86.SDO (DO), D87.SDI (DI)
unnamed: D55.SDO (DO), D56.SDI (DI)
unnamed: D55.CKO (CO), D56.CKI (CI)
unnamed: D54.CKO (CO), D55.CKI (CI)
unnamed: D54.SDO (DO), D55.SDI (DI)
unnamed: D53.SDO (DO), D54.SDI (DI)
unnamed: D53.CKO (CO), D54.CKI (CI)
unnamed: D52.SDO (DO), D53.SDI (DI)
unnamed: D52.CKO (CO), D53.CKI (CI)
unnamed: D51.SDO (DO), D52.SDI (DI)
unnamed: D51.CKO (CO), D52.CKI (CI)
unnamed: D50.CKO (CO), D51.CKI (CI)
unnamed: D50.SDO (DO), D51.SDI (DI)
unnamed: D49.SDO (DO), D50.SDI (DI)
unnamed: D49.CKO (CO), D50.CKI (CI)
unnamed: D87.CKO (CO), D88.CKI (CI)
unnamed: D87.SDO (DO), D88.SDI (DI)
unnamed: D89.CKO (CO), D90.CKI (CI)
unnamed: D89.SDO (DO), D90.SDI (DI)
unnamed: D57.CKO (CO), D58.CKI (CI)
unnamed: D57.SDO (DO), D58.SDI (DI)
unnamed: D58.SDO (DO), D59.SDI (DI)
unnamed: D58.CKO (CO), D59.CKI (CI)
unnamed: D59.CKO (CO), D60.CKI (CI)
unnamed: D59.SDO (DO), D60.SDI (DI)
unnamed: D60.CKO (CO), D61.CKI (CI)
unnamed: D60.SDO (DO), D61.SDI (DI)
unnamed: D61.CKO (CO), D62.CKI (CI)
unnamed: D61.SDO (DO), D62.SDI (DI)
unnamed: D62.SDO (DO), D63.SDI (DI)
unnamed: D62.CKO (CO), D63.CKI (CI)
unnamed: D63.CKO (CO), D64.CKI (CI)
unnamed: D63.SDO (DO), D64.SDI (DI)
unnamed: D90.CKO (CO), D91.CKI (CI)
unnamed: D90.SDO (DO), D91.SDI (DI)
unnamed: D91.CKO (CO), D92.CKI (CI)
unnamed: D91.SDO (DO), D92.SDI (DI)
unnamed: D65.CKO (CO), D66.CKI (CI)
unnamed: D65.SDO (DO), D66.SDI (DI)
unnamed: D66.CKO (CO), D67.CKI (CI)
unnamed: D66.SDO (DO), D67.SDI (DI)
unnamed: D67.CKO (CO), D68.CKI (CI)
unnamed: D67.SDO (DO), D68.SDI (DI)
unnamed: D68.CKO (CO), D69.CKI (CI)
unnamed: D68.SDO (DO), D69.SDI (DI)
unnamed: D69.CKO (CO), D70.CKI (CI)
unnamed: D69.SDO (DO), D70.SDI (DI)
unnamed: D70.CKO (CO), D71.CKI (CI)
unnamed: D70.SDO (DO), D71.SDI (DI)
unnamed: D71.CKO (CO), D72.CKI (CI)
unnamed: D71.SDO (DO), D72.SDI (DI)
unnamed: D137.CKO (CO), D138.CKI (CI)
unnamed: D137.SDO (DO), D138.SDI (DI)
unnamed: D92.CKO (CO), D93.CKI (CI)
unnamed: D92.SDO (DO), D93.SDI (DI)
unnamed: D93.CKO (CO), D94.CKI (CI)
unnamed: D93.SDO (DO), D94.SDI (DI)
unnamed: D94.CKO (CO), D95.CKI (CI)
unnamed: D94.SDO (DO), D95.SDI (DI)
unnamed: D95.CKO (CO), D96.CKI (CI)
unnamed: D95.SDO (DO), D96.SDI (DI)
unnamed: D97.CKO (CO), D98.CKI (CI)
unnamed: D97.SDO (DO), D98.SDI (DI)
unnamed: D98.CKO (CO), D99.CKI (CI)
unnamed: D98.SDO (DO), D99.SDI (DI)
unnamed: D99.CKO (CO), D100.CKI (CI)
unnamed: D99.SDO (DO), D100.SDI (DI)
unnamed: D100.CKO (CO), D101.CKI (CI)
unnamed: D100.SDO (DO), D101.SDI (DI)
unnamed: D101.CKO (CO), D102.CKI (CI)
unnamed: D101.SDO (DO), D102.SDI (DI)
unnamed: D102.CKO (CO), D103.CKI (CI)
unnamed: D102.SDO (DO), D103.SDI (DI)
unnamed: D103.CKO (CO), D104.CKI (CI)
unnamed: D103.SDO (DO), D104.SDI (DI)
unnamed: D111.CKO (CO), D112.CKI (CI)
unnamed: D111.SDO (DO), D112.SDI (DI)
unnamed: D110.SDO (DO), D111.SDI (DI)
unnamed: D110.CKO (CO), D111.CKI (CI)
unnamed: D109.SDO (DO), D110.SDI (DI)
unnamed: D109.CKO (CO), D110.CKI (CI)
unnamed: D108.SDO (DO), D109.SDI (DI)
unnamed: D108.CKO (CO), D109.CKI (CI)
unnamed: D107.SDO (DO), D108.SDI (DI)
unnamed: D107.CKO (CO), D108.CKI (CI)
unnamed: D106.SDO (DO), D107.SDI (DI)
unnamed: D106.CKO (CO), D107.CKI (CI)
unnamed: D105.CKO (CO), D106.CKI (CI)
unnamed: D105.SDO (DO), D106.SDI (DI)
unnamed: D113.CKO (CO), D114.CKI (CI)
unnamed: D113.SDO (DO), D114.SDI (DI)
unnamed: D114.CKO (CO), D115.CKI (CI)
unnamed: D114.SDO (DO), D115.SDI (DI)
unnamed: D115.CKO (CO), D116.CKI (CI)
unnamed: D115.SDO (DO), D116.SDI (DI)
unnamed: D116.CKO (CO), D117.CKI (CI)
unnamed: D116.SDO (DO), D117.SDI (DI)
unnamed: D117.SDO (DO), D118.SDI (DI)
unnamed: D117.CKO (CO), D118.CKI (CI)
unnamed: D118.CKO (CO), D119.CKI (CI)
unnamed: D118.SDO (DO), D119.SDI (DI)
unnamed: D119.CKO (CO), D120.CKI (CI)
unnamed: D119.SDO (DO), D120.SDI (DI)
unnamed: D127.SDO (DO), D128.SDI (DI)
unnamed: D127.CKO (CO), D128.CKI (CI)
unnamed: D126.CKO (CO), D127.CKI (CI)
unnamed: D126.SDO (DO), D127.SDI (DI)
unnamed: D125.SDO (DO), D126.SDI (DI)
unnamed: D125.CKO (CO), D126.CKI (CI)
unnamed: D124.SDO (DO), D125.SDI (DI)
unnamed: D124.CKO (CO), D125.CKI (CI)
unnamed: D123.SDO (DO), D124.SDI (DI)
unnamed: D123.CKO (CO), D124.CKI (CI)
unnamed: D122.CKO (CO), D123.CKI (CI)
unnamed: D122.SDO (DO), D123.SDI (DI)
unnamed: D121.SDO (DO), D122.SDI (DI)
unnamed: D121.CKO (CO), D122.CKI (CI)
unnamed: C1.1, U1.42 (AREF)
unnamed: C4.2, U1.17 (XTAL1), Y1.3 (2)
unnamed: C5.2, U1.16 (XTAL2), Y1.1
unnamed: C3.1, U1.6 (UCAP)
unnamed: RPROG0.1, U2.5 (PROG)
unnamed: J1.D+, R3.2
unnamed: J1.D-, R2.2
unnamed: R4.1, R5.2, U3.5 (FB)
unnamed: L1.P$2 (2), U3.1 (LX)
unnamed: BT1.PWR@1 (+), S2.1, S2.4
unnamed: D138.CKO (CO), D139.CKI (CI)
unnamed: D138.SDO (DO), D139.SDI (DI)
unnamed: D139.CKO (CO), D140.CKI (CI)
unnamed: D139.SDO (DO), D140.SDI (DI)
unnamed: D140.CKO (CO), D141.CKI (CI)
unnamed: D140.SDO (DO), D141.SDI (DI)
unnamed: D141.CKO (CO), D142.CKI (CI)
unnamed: D141.SDO (DO), D142.SDI (DI)
unnamed: D142.CKO (CO), D143.CKI (CI)
unnamed: D142.SDO (DO), D143.SDI (DI)
unnamed: D143.CKO (CO), D144.CKI (CI)
unnamed: D143.SDO (DO), D144.SDI (DI)
R1CK: D1.CKI (CI), J10.3, U1.9 (PB1(SCK))
R1DA: D1.SDI (DI), J10.4, U1.10 (PB2(MOSI))
R2CK: D8.CKO (CO), D9.CKI (CI)
R2DA: D8.SDO (DO), D9.SDI (DI)
R3CK: D16.CKO (CO), D17.CKI (CI)
R3DA: D16.SDO (DO), D17.SDI (DI)
R4CK: D24.CKO (CO), D25.CKI (CI)
R4DA: D24.SDO (DO), D25.SDI (DI)
R5CK: D32.CKO (CO), D33.CKI (CI)
R5DA: D32.SDO (DO), D33.SDI (DI)
R6CK: D40.CKO (CO), D41.CKI (CI)
R6DA: D40.SDO (DO), D41.SDI (DI)
R7CK: D48.CKO (CO), D49.CKI (CI)
R7DA: D48.SDO (DO), D49.SDI (DI)
R8CK: D56.CKO (CO), D57.CKI (CI)
R8DA: D56.SDO (DO), D57.SDI (DI)
R9CK: D64.CKO (CO), D65.CKI (CI)
R9DA: D64.SDO (DO), D65.SDI (DI)
R10CK: D72.CKO (CO), D137.CKI (CI)
R10DA: D72.SDO (DO), D137.SDI (DI)
R11CK: D73.CKI (CI), D144.CKO (CO)
R11DA: D73.SDI (DI), D144.SDO (DO)
R12CK: D80.CKO (CO), D81.CKI (CI)
R12DA: D80.SDO (DO), D81.SDI (DI)
R13CK: D88.CKO (CO), D89.CKI (CI)
R13DA: D88.SDO (DO), D89.SDI (DI)
R14CK: D96.CKO (CO), D97.CKI (CI)
R14DA: D96.SDO (DO), D97.SDI (DI)
R15CK: D104.CKO (CO), D105.CKI (CI)
R15DA: D104.SDO (DO), D105.SDI (DI)
R16CK: D112.CKO (CO), D113.CKI (CI)
R16DA: D112.SDO (DO), D113.SDI (DI)
R17CK: D120.CKO (CO), D121.CKI (CI)
R17DA: D120.SDO (DO), D121.SDI (DI)
R18CK: D128.CKO (CO)
R18DA: D128.SDO (DO)
RIGHT: J5.1, U1.30 (PB6(ADC13))
VBATT: C8.1, C10.1, L1.P$1 (1), R6.2, S2.2, S2.5, U2.3 (VBAT), U3.3 (VIN)
VCC: C2.1, C6.1, C7.1, D1.VDD (VCC), D2.VDD (VCC), D3.VDD (VCC), D4.VDD (VCC), D5.VDD (VCC), D6.VDD (VCC), D7.VDD (VCC), D8.VDD (VCC), D9.VDD (VCC), D10.VDD (VCC), D11.VDD (VCC), D12.VDD (VCC), D13.VDD (VCC), D14.VDD (VCC), D15.VDD (VCC), D16.VDD (VCC), D17.VDD (VCC), D18.VDD (VCC), D19.VDD (VCC), D20.VDD (VCC), D21.VDD (VCC), D22.VDD (VCC), D23.VDD (VCC), D24.VDD (VCC), D25.VDD (VCC), D26.VDD (VCC), D27.VDD (VCC), D28.VDD (VCC), D29.VDD (VCC), D30.VDD (VCC), D31.VDD (VCC), D32.VDD (VCC), D33.VDD (VCC), D34.VDD (VCC), D35.VDD (VCC), D36.VDD (VCC), D37.VDD (VCC), D38.VDD (VCC), D39.VDD (VCC), D40.VDD (VCC), D41.VDD (VCC), D42.VDD (VCC), D43.VDD (VCC), D44.VDD (VCC), D45.VDD (VCC), D46.VDD (VCC), D47.VDD (VCC), D48.VDD (VCC), D49.VDD (VCC), D50.VDD (VCC), D51.VDD (VCC), D52.VDD (VCC), D53.VDD (VCC), D54.VDD (VCC), D55.VDD (VCC), D56.VDD (VCC), D57.VDD (VCC), D58.VDD (VCC), D59.VDD (VCC), D60.VDD (VCC), D61.VDD (VCC), D62.VDD (VCC), D63.VDD (VCC), D64.VDD (VCC), D65.VDD (VCC), D66.VDD (VCC), D67.VDD (VCC), D68.VDD (VCC), D69.VDD (VCC), D70.VDD (VCC), D71.VDD (VCC), D72.VDD (VCC), D73.VDD (VCC), D74.VDD (VCC), D75.VDD (VCC), D76.VDD (VCC), D77.VDD (VCC), D78.VDD (VCC), D79.VDD (VCC), D80.VDD (VCC), D81.VDD (VCC), D82.VDD (VCC), D83.VDD (VCC), D84.VDD (VCC), D85.VDD (VCC), D86.VDD (VCC), D87.VDD (VCC), D88.VDD (VCC), D89.VDD (VCC), D90.VDD (VCC), D91.VDD (VCC), D92.VDD (VCC), D93.VDD (VCC), D94.VDD (VCC), D95.VDD (VCC), D96.VDD (VCC), D97.VDD (VCC), D98.VDD (VCC), D99.VDD (VCC), D100.VDD (VCC), D101.VDD (VCC), D102.VDD (VCC), D103.VDD (VCC), D104.VDD (VCC), D105.VDD (VCC), D106.VDD (VCC), D107.VDD (VCC), D108.VDD (VCC)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
~RST: J10.5, R1.1, U1.13 (~RESET)

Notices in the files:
projects/npoole_evacuation_bench_controller_bench_controller/current_version/working/working.kicad_sch:
https://creativecommons.org/licenses/by-sa/4.0
Released under the Creative Commons
parts and their libraries:
Released under the Creative Commons Attribution Share-Alike 4.0 License
